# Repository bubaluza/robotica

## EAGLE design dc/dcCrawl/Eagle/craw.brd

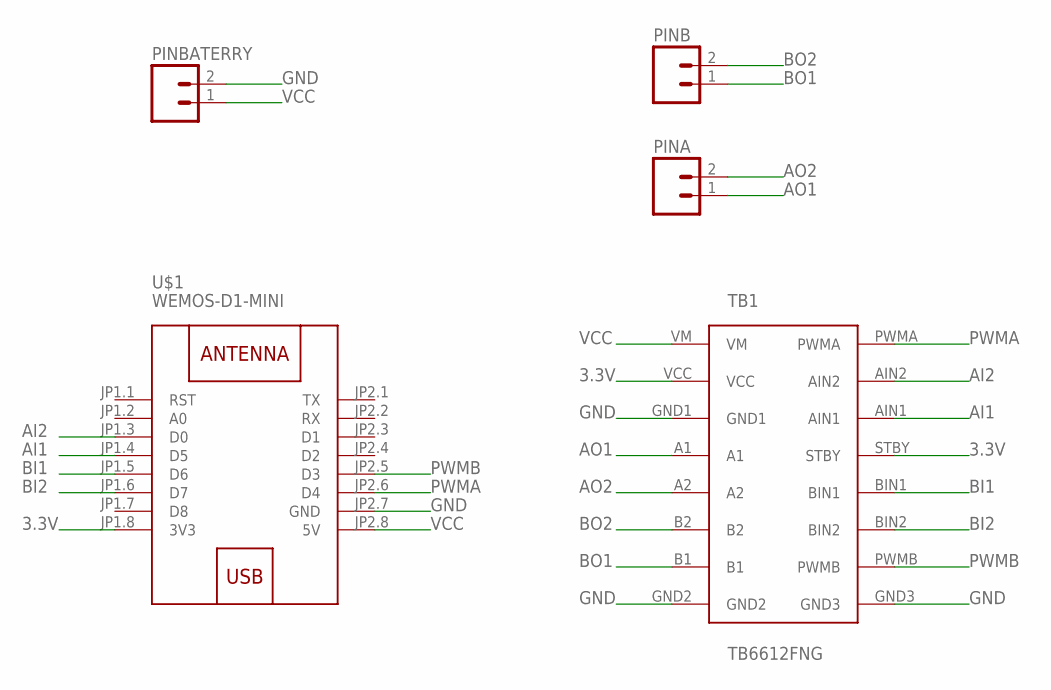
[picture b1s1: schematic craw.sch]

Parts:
PINA: M02; 02P
PINB: M02; 02P
PINBATERRY: M02; 02P
TB1: TB6612FNG
U$1: WEMOS-D1-MINI

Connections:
3.3V: TB1.STBY, TB1.VCC, U$1.JP1.8 (3V3)
AI1: TB1.AIN1, U$1.JP1.4 (D5)
AI2: TB1.AIN2, U$1.JP1.3 (D0)
AO1: PINA.1, TB1.A1
AO2: PINA.2, TB1.A2
BI1: TB1.BIN1, U$1.JP1.5 (D6)
BI2: TB1.BIN2, U$1.JP1.6 (D7)
BO1: PINB.1, TB1.B1
BO2: PINB.2, TB1.B2
GND: PINBATERRY.2, TB1.GND1, TB1.GND2, TB1.GND3, U$1.JP2.7 (GND)
PWMA: TB1.PWMA, U$1.JP2.6 (D4)
PWMB: TB1.PWMB, U$1.JP2.5 (D3)
VCC: PINBATERRY.1, TB1.VM, U$1.JP2.8 (5V)

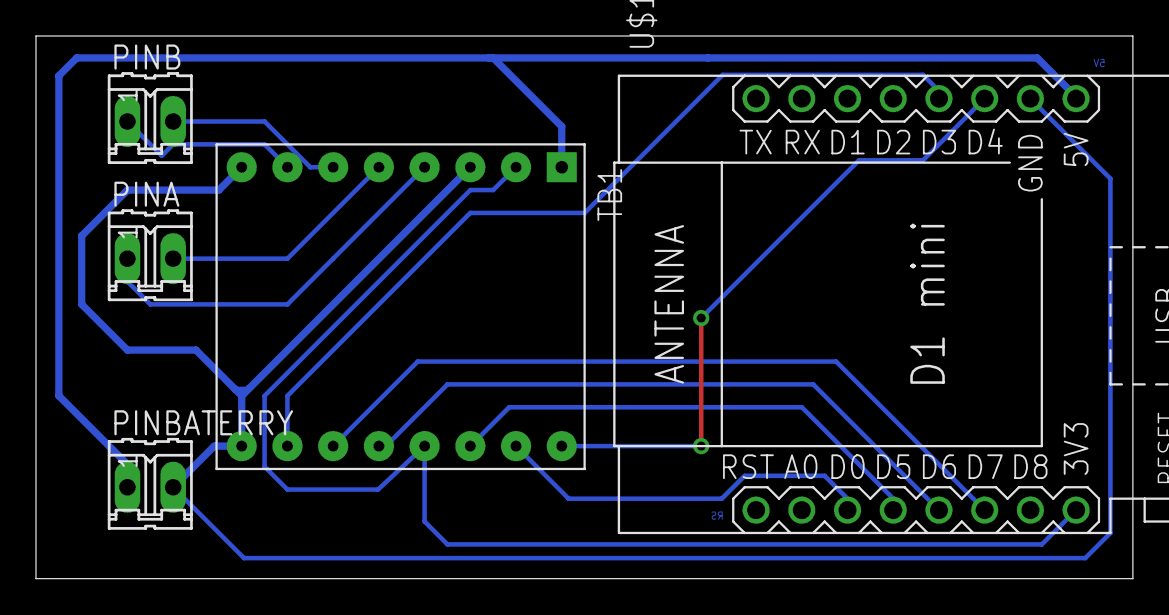
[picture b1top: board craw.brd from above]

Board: 2 copper layers, 60.9 x 30.2 mm, 5 parts (0 on the bottom side), 13 nets.

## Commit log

2019-03-26 init
2019-03-26 readme fix
2019-03-26 readme fixv2
2019-03-26 deleted useless thing, .ino not yet with serialcomunication inside
2019-04-03 serialStepper esp8266
2019-04-16 upgrade stepper.ino
2019-04-17 upgrade esp8266 stepperSerial firmware
2019-04-17 minor fix && calibration invertion
2019-04-17 bug fix
2019-04-17 mass fix
2019-05-07 DC crawl arduino && Eagle
2019-06-05 motor
2020-12-11 Bump ini from 1.3.5 to 1.3.7 in /esp32NodeSerial
    Bumps [ini](https://github.com/isaacs/ini) from 1.3.5 to 1.3.7.
    - [Release notes](https://github.com/isaacs/ini/releases)
    - [Commits](https://github.com/isaacs/ini/compare/v1.3.5...v1.3.7)
2022-02-10 Bump undefsafe from 2.0.2 to 2.0.5 in /esp32NodeSerial
    Bumps [undefsafe](https://github.com/remy/undefsafe) from 2.0.2 to 2.0.5.
    - [Release notes](https://github.com/remy/undefsafe/releases)
    - [Commits](https://github.com/remy/undefsafe/compare/v2.0.2...v2.0.5)
    ---
    updated-dependencies:
    - dependency-name: undefsafe
2022-12-03 Bump decode-uri-component from 0.2.0 to 0.2.2 in /esp32NodeSerial
    Bumps [decode-uri-component](https://github.com/SamVerschueren/decode-uri-component) from 0.2.0 to 0.2.2.
    - [Release notes](https://github.com/SamVerschueren/decode-uri-component/releases)
    - [Commits](https://github.com/SamVerschueren/decode-uri-component/compare/v0.2.0...v0.2.2)
    ---
    updated-dependencies:
    - dependency-name: decode-uri-component
2022-12-06 Bump qs, body-parser and express in /esp32NodeSerial
    Bumps [qs](https://github.com/ljharb/qs) to 6.11.0 and updates ancestor dependencies [qs](https://github.com/ljharb/qs), [body-parser](https://github.com/expressjs/body-parser) and [express](https://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
    Updates `qs` from 6.5.2 to 6.11.0
    - [Release notes](https://github.com/ljharb/qs/releases)
    - [Changelog](https://github.com/ljharb/qs/blob/main/CHANGELOG.md)
    - [Commits](https://github.com/ljharb/qs/compare/v6.5.2...v6.11.0)
    Updates `body-parser` from 1.19.0 to 1.20.1
2022-12-10 Bump express from 4.16.4 to 4.17.3 in /esp32NodeSerial
    Bumps [express](https://github.com/expressjs/express) from 4.16.4 to 4.17.3.
    - [Release notes](https://github.com/expressjs/express/releases)
    - [Changelog](https://github.com/expressjs/express/blob/master/History.md)
    - [Commits](https://github.com/expressjs/express/compare/4.16.4...4.17.3)
    ---
    updated-dependencies:

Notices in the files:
parts and their libraries:
diy-modules: Released under the Creative Commons Attribution 4.0 International License: http://creativecommons.org/licenses/by/4.0
